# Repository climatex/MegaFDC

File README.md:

# MegaFDC
Arduino Mega2560 floppy disk controller.

Supports 8" / 5.25" / 3.5" drives (PS/2 2.88MB included) with custom geometry, FAT12 and experimental CP/M.

Interfaces via USB/RS232, also through keyboard and display.

# More information
Check out my [website article](http://boginjr.com/it/hw/megafdc) to learn more!

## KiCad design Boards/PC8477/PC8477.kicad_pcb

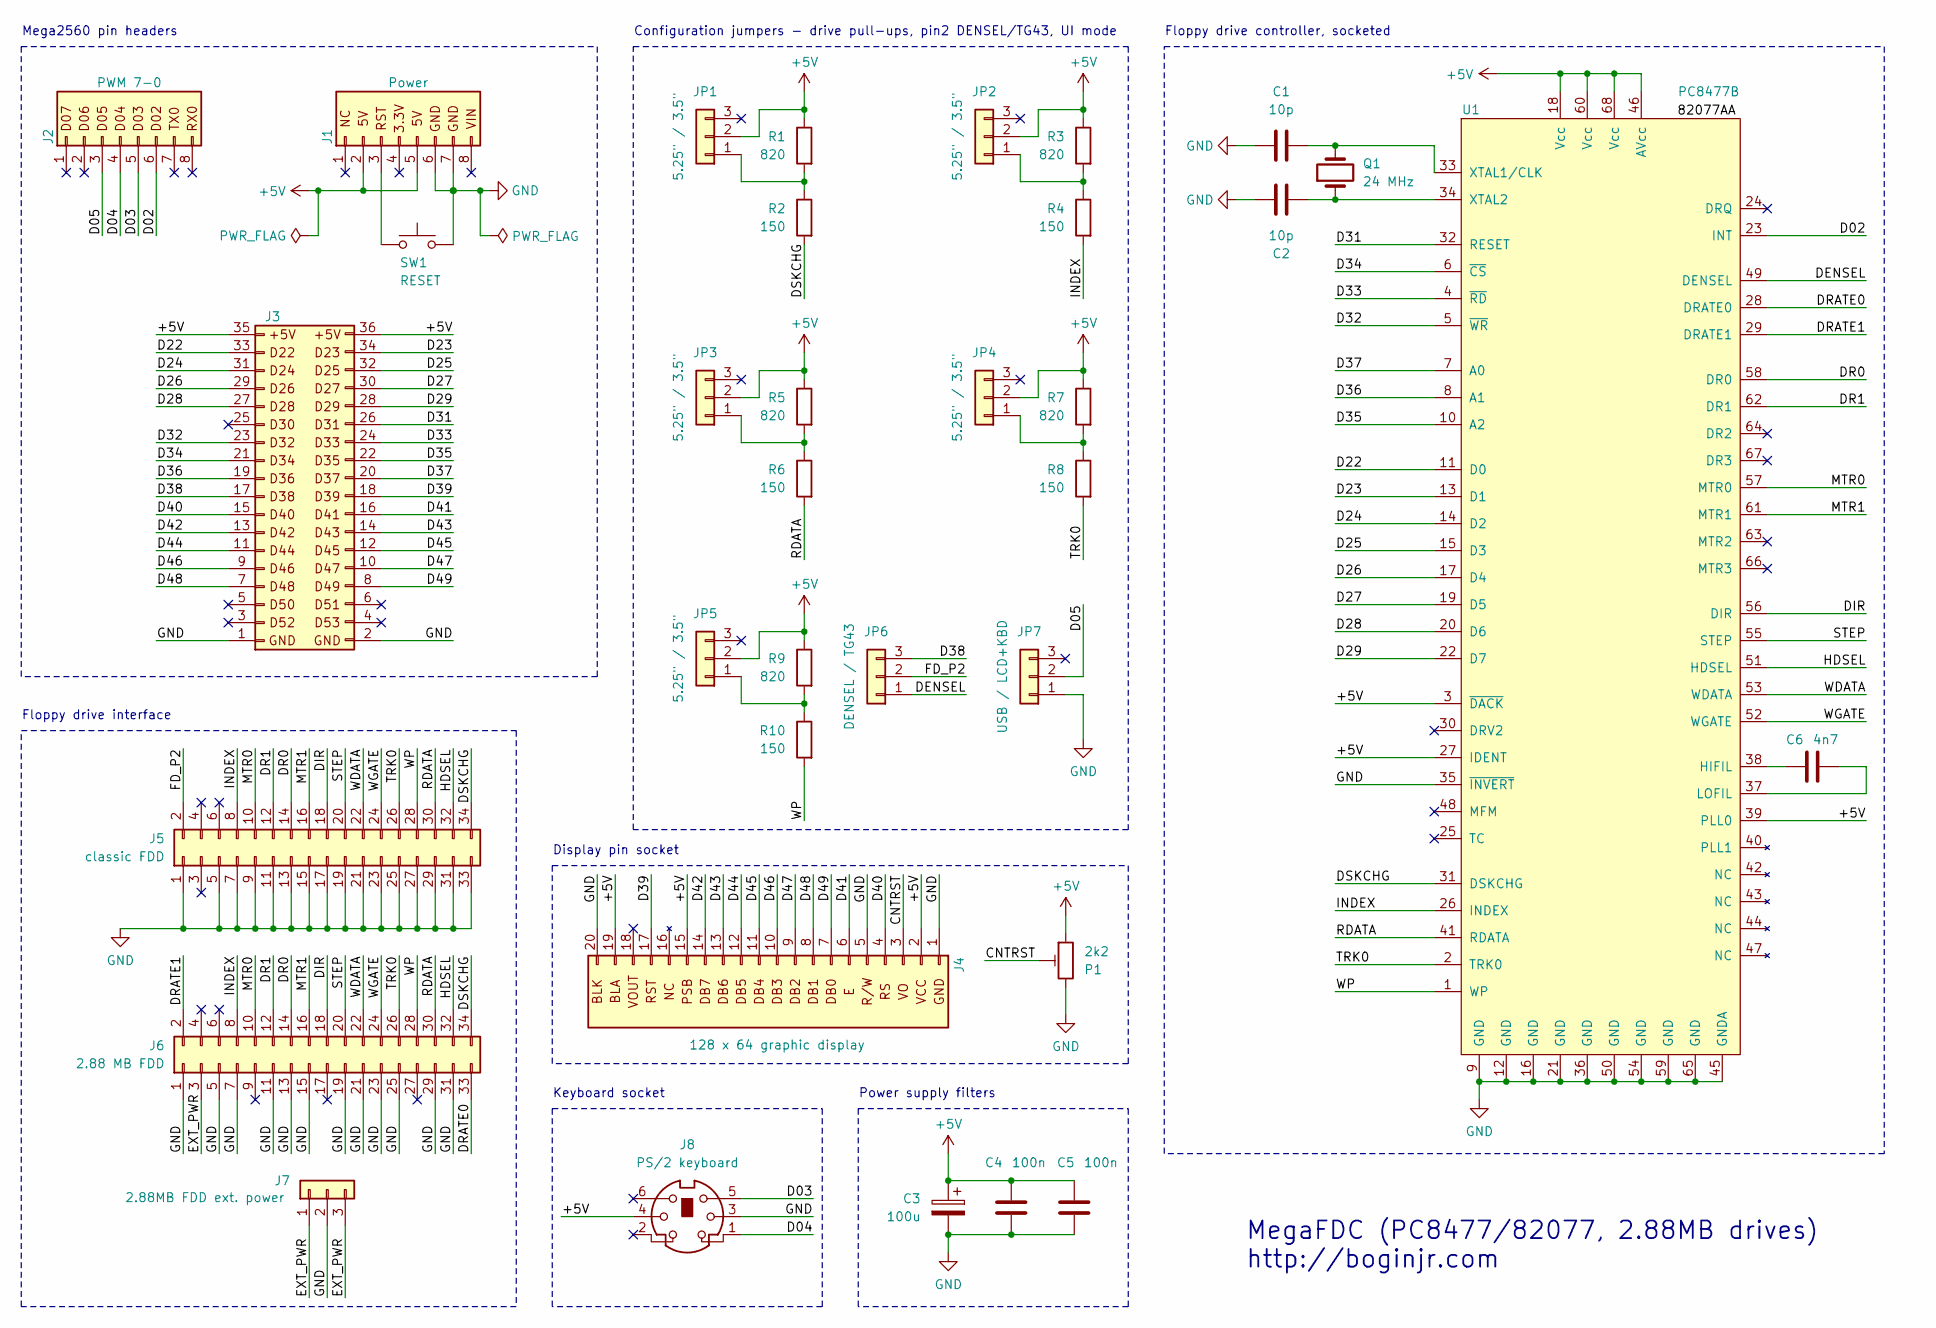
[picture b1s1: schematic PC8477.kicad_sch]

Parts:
C1, C2: 10p; C_Disc_D7.5mm_W2.5mm_P5.00mm
C3: 100u; CP_Radial_D6.3mm_P2.50mm
C4, C5: 100n; C_Disc_D7.5mm_W2.5mm_P5.00mm
C6: 4n7; C_Disc_D7.5mm_W2.5mm_P5.00mm
J1: Power; PinHeader_1x08_P2.54mm_Vertical
J2: PWM 7-0; PinHeader_1x08_P2.54mm_Vertical
J3: Digital; PinHeader_2x18_P2.54mm_Vertical
J4: 128 x 64 graphic display; PinSocket_1x20_P2.54mm_Vertical
J5: classic FDD; PinHeader_2x17_P2.54mm_Vertical
J6: 2.88 MB FDD; PinHeader_2x17_P2.54mm_Vertical
J7: 2.88MB FDD ext. power; PinHeader_1x03_P2.54mm_Vertical
J8: PS/2 keyboard; Mini_DIN6_Female_THT
JP1, JP2, JP3, JP4, JP5: 5.25" / 3.5"; PinHeader_1x03_P2.54mm_Vertical
JP6: DENSEL / TG43; PinHeader_1x03_P2.54mm_Vertical
JP7: USB / LCD+KBD; PinHeader_1x03_P2.54mm_Vertical
P1: 2k2; Potentiometer_Bourns_3386P_Vertical
Q1: 24 MHz; Crystal_HC49-U_Vertical
R1, R3, R5, R7, R9: 820; R_Axial_DIN0207_L6.3mm_D2.5mm_P10.16mm_Horizontal
R2, R4, R6, R8, R10: 150; R_Axial_DIN0207_L6.3mm_D2.5mm_P10.16mm_Horizontal
SW1: RESET; SW_PUSH_6mm
U1: PC8477B; PLCC-68_THT-Socket

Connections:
+5V: C3.1, C4.1, C5.1, J1.2, J1.5, J3.35, J3.36, J4.2, J4.15, J4.19, J8.4, JP1.2, JP2.2, JP3.2, JP4.2, JP5.2, P1.1, R1.1, R3.1, R5.1, R7.1, R9.1, U1.3 (~DACK), U1.18 (Vcc), U1.27 (IDENT), U1.39 (PLL0), U1.46 (AVcc), U1.60 (Vcc), U1.68 (Vcc)
/CNTRST: J4.3, P1.2
/D02: J2.6, U1.23 (INT)
/D03: J2.5, J8.5
/D04: J2.4, J8.1
/D05: J2.3, JP7.2
/D22: J3.33, U1.11 (D0)
/D23: J3.34, U1.13 (D1)
/D24: J3.31, U1.14 (D2)
/D25: J3.32, U1.15 (D3)
/D26: J3.29, U1.17 (D4)
/D27: J3.30, U1.19 (D5)
/D28: J3.27, U1.20 (D6)
/D29: J3.28, U1.22 (D7)
/D31: J3.26, U1.32 (RESET)
/D32: J3.23, U1.5 (~WR)
/D33: J3.24, U1.4 (~RD)
/D34: J3.21, U1.6 (~CS)
/D35: J3.22, U1.10 (A2)
/D36: J3.19, U1.8 (A1)
/D37: J3.20, U1.7 (A0)
/D38: J3.17, JP6.3
/D39: J3.18, J4.17
/D40: J3.15, J4.4
/D41: J3.16, J4.6
/D42: J3.13, J4.14
/D43: J3.14, J4.13
/D44: J3.11, J4.12
/D45: J3.12, J4.11
/D46: J3.9, J4.10
/D47: J3.10, J4.9
/D48: J3.7, J4.8
/D49: J3.8, J4.7
/DENSEL: JP6.1, U1.49 (DENSEL)
/DIR: J5.18, J6.18, U1.56 (DIR)
/DR0: J5.14, J6.14, U1.58 (DR0)
/DR1: J5.12, J6.12, U1.62 (DR1)
/DRATE0: J6.33, U1.28 (DRATE0)
/DRATE1: J6.2, U1.29 (DRATE1)
/DSKCHG: J5.34, J6.34, R2.2, U1.31 (DSKCHG)
/EXT_PWR: J6.3, J7.1, J7.3
/FD_P2: J5.2, JP6.2
/HDSEL: J5.32, J6.32, U1.51 (HDSEL)
/INDEX: J5.8, J6.8, R4.2, U1.26 (INDEX)
/MTR0: J5.10, J6.10, U1.57 (MTR0)
/MTR1: J5.16, J6.16, U1.61 (MTR1)
/RDATA: J5.30, J6.30, R6.2, U1.41 (RDATA)
/STEP: J5.20, J6.20, U1.55 (STEP)
/TRK0: J5.26, J6.26, R8.2, U1.2 (TRK0)
/WDATA: J5.22, J6.22, U1.53 (WDATA)
/WGATE: J5.24, J6.24, U1.52 (WGATE)
/WP: J5.28, J6.28, R10.2, U1.1 (WP)
GND: C1.1, C2.1, C3.2, C4.2, C5.2, J1.6, J1.7, J3.1, J3.2, J4.1, J4.5, J4.20, J5.1, J5.5, J5.7, J5.9, J5.11, J5.13, J5.15, J5.17, J5.19, J5.21, J5.23, J5.25, J5.27, J5.29, J5.31, J5.33, J6.1, J6.5, J6.7, J6.11, J6.13, J6.15, J6.19, J6.21, J6.23, J6.25, J6.29, J6.31, J7.2, J8.3, J8.SH1, J8.SH2, J8.SH3, JP7.1, P1.3, SW1.1, U1.9 (GND), U1.12 (GND), U1.16 (GND), U1.21 (GND), U1.35 (~INVERT), U1.36 (GND), U1.45 (GNDA), U1.50 (GND), U1.54 (GND), U1.59 (GND), U1.65 (GND)
unnamed: J1.3, SW1.2
unnamed: JP1.1, R1.2, R2.1
unnamed: JP2.1, R3.2, R4.1
unnamed: JP3.1, R5.2, R6.1
unnamed: JP4.1, R7.2, R8.1
unnamed: JP5.1, R9.2, R10.1
unnamed: C6.2, U1.38 (HIFIL)
unnamed: C6.1, U1.37 (LOFIL)
unnamed: C1.2, Q1.2, U1.33 (XTAL1/CLK)
unnamed: C2.2, Q1.1, U1.34 (XTAL2)

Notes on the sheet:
Configuration jumpers - drive pull-ups, pin2 DENSEL/TG43, UI mode
Keyboard socket
Floppy drive interface
Power supply filters
MegaFDC (PC8477/82077, 2.88MB drives) http://boginjr.com
Display pin socket
Floppy drive controller, socketed
Mega2560 pin headers

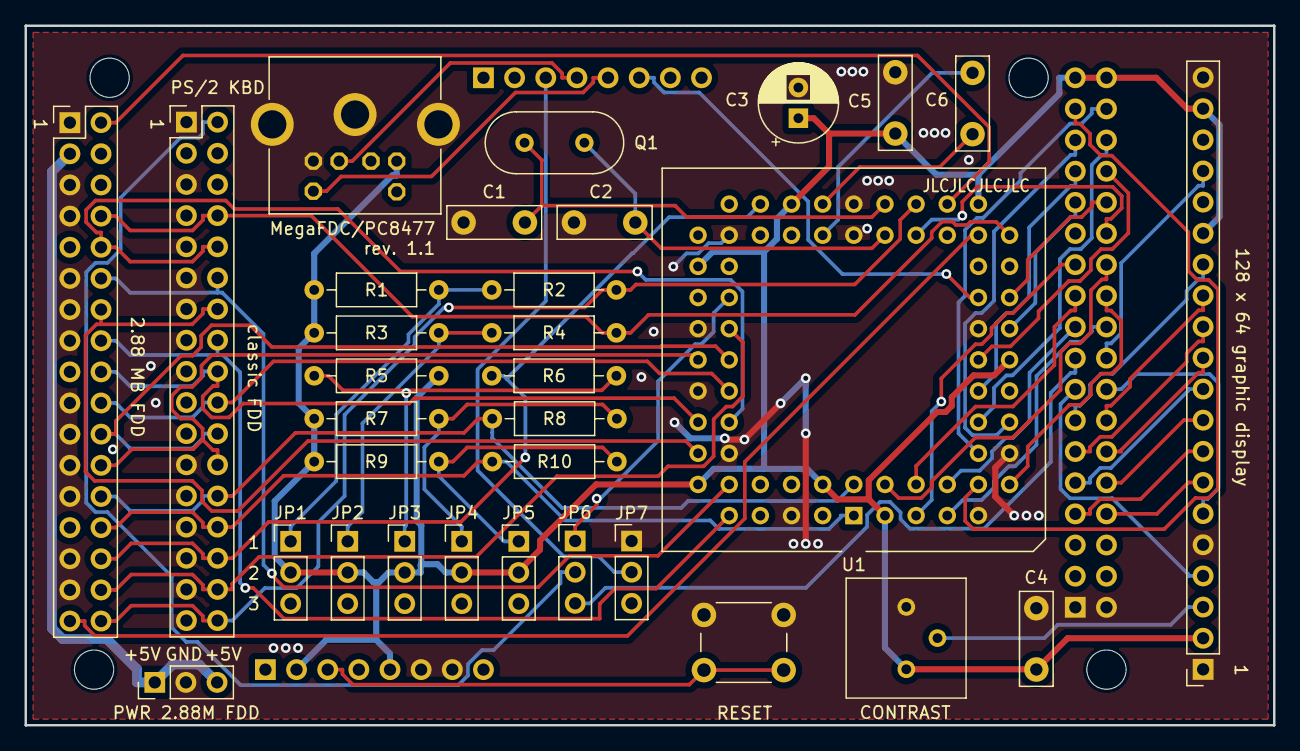
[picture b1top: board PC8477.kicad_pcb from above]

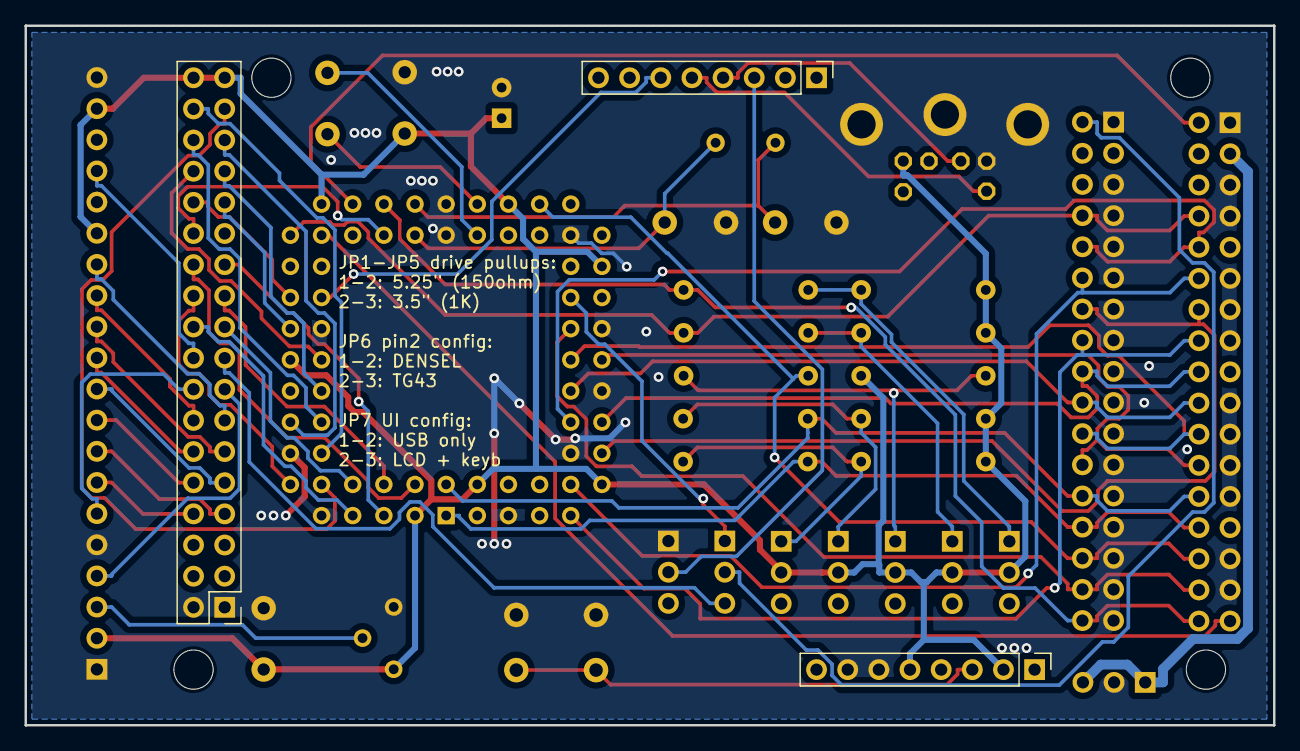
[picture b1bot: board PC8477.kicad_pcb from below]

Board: 2 copper layers, 101.8 x 57.0 mm, 39 parts (3 on the bottom side), 63 nets.

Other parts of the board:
MH1, MH2, MH5, MH6: MountingHole_3.2mm

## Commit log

2023-03-14 Unset FDC_ISR_ASSEMBLY by default
2023-03-15 Fix double-stepping
2023-07-04 Handle TG43 on PD7, wait 2 cycles for FDC, CP/M root dir bugfixes
2023-07-24 Do seek test on drive select, comment on TG43 in config.h
2023-08-18 Add boards and schematics, FIFO buffer support, perpendicular recording, bugfixes
2023-08-28 Update web links, inform about formatting with verify if writing filesystem
2023-08-30 Speed up FAT file I/O by turning off the Tiny buffer
2024-11-24 Add ImageDisk (IMD) support, bugfixes
2024-11-28 Set stepper to 16ms for an 8" CDC drive, bugfix in DRIVPARM
2025-03-30 Improve interleave detection in IMD mode; bugfixes
2025-05-26 Build 26th of May 2025 changes:
    - UI with LCD output now doesn't require a physical keyboard,
    - TYPEINTO command opens files with append instead of truncate,
    - bugfix in the DELAY_MS macro,
    - DP8473 Kicad schematic parts numbers reordered to match the Eagle PCB.
2025-06-26 Build 26th of June 2025 changes:
    - IMD mode: sector 0 compatibility,
    - IMD mode format command: customizable starting sector,
    - both modes: better distinguish between track and a cylinder in code and strings.
2025-06-27 Sync with Winchesterduino
2025-07-21 Classic mode: bugfix in getMaximumSectorCount()
2026-02-22 Add SD support, remember settings in IMD mode, bugfixes
2026-02-27 Small fix for Num Lock
